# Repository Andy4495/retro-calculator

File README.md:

# Retro Calculator

![Retro Calculator Image][8]

After seeing an Arduino Project Hub [article][5], I purchased a handful of [NSA1166][2] bubble LED displays from [Jameco][3] and decided to build a [retro calculator][8].

The calculator uses an [MSP430G2553][9] microcontroller and [ICM7228][10] LED driver along with a generic 4x4 matrix keypad.

To make the project as small as possible and to simplify the wiring, I created created a PCB design and ordered it from [OshPark][11].

Due to limitations of my keypad and the display (6 characters with a single fixed decimal point), the calculator only supports limited functions and integer math.

## Hardware

The Eagle BRD and SCH files can be found in the [hardware folder][12], along with a PDF of the [schematic][14].

## External Libraries

The calculator uses my [matrix keypad library][1] and [ICM7218 LED driver library][15].

## References

* Arduino Project Hub [article][5]
* NSA-1166 [datasheet][2]
* NSA-1166 devices at [Jameco][3]
* [MSP430G2553][9]
* [ICM7228][10]
* [Schematic][14]
* [Library][4] written specifically for NSA1166, without using discrete controller IC
* Vintage Novus 650 Mathbox [calculator][6] that used the NSA1166 display, including [interior pictures][7]

## License

The software and other files in this repository are released under what is commonly called the [MIT License][100]. See the file [`LICENSE`][101] in this repository.

[1]: https://github.com/Andy4495/matrix-keypad-library
[2]: https://www.jameco.com/Jameco/Products/ProdDS/2210976NAT.pdf
[3]: https://www.jameco.com/z/NSA1166-National-Semiconductor-LED-Display-7-Segment-Red-0-10-Inch-6-Digit-1-65V-5mA-2-Inch-Long_2210976.html
[4]: https://github.com/8bitkick/SevSegPlus
[5]: https://create.arduino.cc/projecthub/8bitkick/retro-led-bubble-display-d357e9
[6]: https://www.keesvandersanden.nl/calculators/novus650.php
[7]: https://www.keesvandersanden.nl/calculators/novus650_inside.php
[8]: ./hardware/Calculator.jpeg
[9]: https://www.ti.com/product/MSP430G2553
[10]: https://www.renesas.com/us/en/www/doc/datasheet/icm7228.pdf
[11]: https://oshpark.com/
[12]: ./hardware
[14]: ./hardware/retro-calculator-schematic.pdf
[15]: https://github.com/Andy4495/ICM7218
[100]: https://choosealicense.com/licenses/mit/
[101]: ./LICENSE
[//]: # ([200]: https://github.com/Andy4495/retro-calculator)

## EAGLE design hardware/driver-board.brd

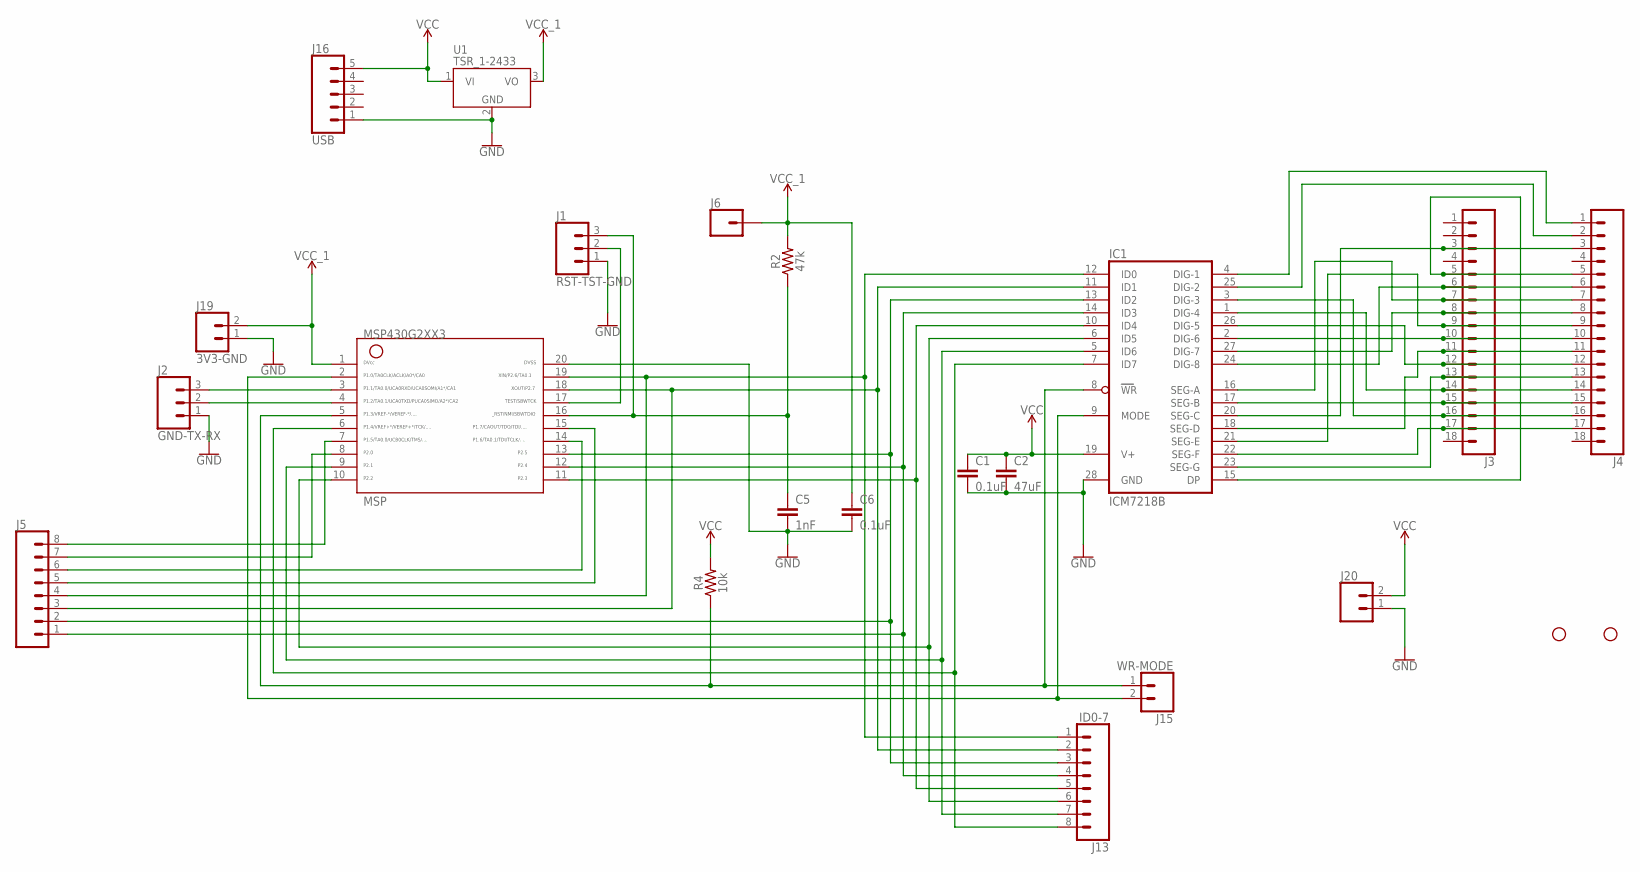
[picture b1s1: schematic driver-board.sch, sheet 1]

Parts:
C1: 0.1uF; C2.5-2
C2: 47uF; C2.5-5
C5: 1nF; C5B2.5
C6: 0.1uF; C5B2.5
H1, H2: STAND-OFF
IC1: ICM7218B; DIL28-6
J1: RST-TST-GND; 1X03_LOCK
J2: GND-TX-RX; 1X03_LOCK
J3, J4: CONN_18; 1X18
J5: CONN_08"; 1X08
J6: CONN_01; 1X01
J13: ID0-7; 1X08_LOCK
J15: WR-MODE; 1X02
J16: USB; 1X05_LOCK
J19: 3V3-GND; 1X02
J20: CONN_02; 1X02
MSP: G2XX3---N20; N20
R2: 47k; AXIAL-0.3
R4: 10k; AXIAL-0.3
U1: TSR_1-2433; TSR-1

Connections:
GND: C1.2, C2.2, C5.2, C6.2, IC1.28 (GND), J1.1, J2.1, J16.1, J19.1, J20.1, MSP.20, U1.2 (GND)
unnamed: IC1.3 (DIG-3), J3.16, J4.16
unnamed: IC1.1 (DIG-4), J3.14, J4.14
unnamed: IC1.26 (DIG-5), J3.12, J4.12
unnamed: J5.8, MSP.7
unnamed: IC1.2 (DIG-6), J3.10, J4.10
unnamed: IC1.27 (DIG-7), J3.8, J4.8
unnamed: IC1.15 (DP), J3.5, J4.5
unnamed: IC1.23 (SEG-G), J3.13, J4.13
unnamed: IC1.24 (DIG-8), J3.6, J4.6
unnamed: IC1.22 (SEG-F), J3.17, J4.17
unnamed: IC1.20 (SEG-C), J3.3, J4.3
unnamed: J5.7, MSP.8
unnamed: IC1.17 (SEG-B), J3.15, J4.15
unnamed: IC1.18 (SEG-D), J3.11, J4.11
unnamed: IC1.21 (SEG-E), J3.9, J4.9
unnamed: IC1.16 (SEG-A), J3.7, J4.7
unnamed: IC1.25 (DIG-2), J4.2
unnamed: IC1.4 (DIG-1), J4.1
unnamed: J2.2, MSP.4
unnamed: J5.6, MSP.14
unnamed: C5.1, J1.3, MSP.16, R2.P$1 (1)
unnamed: J5.5, MSP.15
unnamed: J1.2, MSP.17
unnamed: IC1.14 (ID3), J5.1, J13.4, MSP.12
unnamed: IC1.10 (ID4), J13.5, MSP.11
unnamed: IC1.12 (ID0), J5.4, J13.1, MSP.19
unnamed: IC1.11 (ID1), J5.3, J13.2, MSP.18
unnamed: IC1.6 (ID5), J13.6, MSP.10
unnamed: IC1.5 (ID6), J13.7, MSP.9
unnamed: IC1.7 (ID7), J13.8, MSP.6
unnamed: IC1.8 (WR), J15.1, MSP.5, R4.P$1 (1)
unnamed: IC1.9 (MODE), J15.2, MSP.2
unnamed: J2.3, MSP.3
unnamed: IC1.13 (ID2), J5.2, J13.3, MSP.13
VCC: C1.1, C2.1, IC1.19 (V+), J16.5, J20.2, R4.P$2 (2), U1.1 (VI)
VCC_1: C6.1, J6.1, J19.2, MSP.1, R2.P$2 (2), U1.3 (VO)

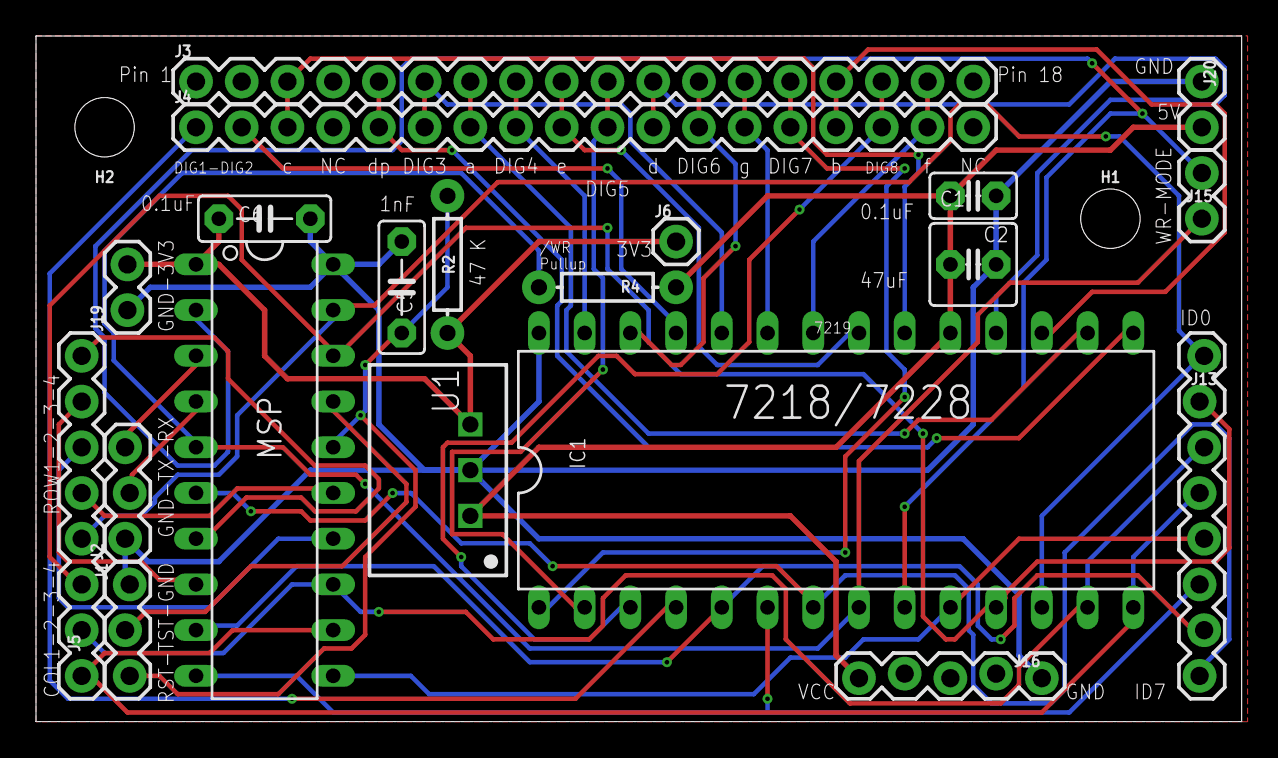
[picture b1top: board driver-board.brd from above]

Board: 2 copper layers, 67.0 x 38.1 mm, 22 parts (0 on the bottom side), 37 nets.

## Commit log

2019-04-12 Original working version.
2019-12-03 Add readme, schematic, eagle files, photo.
2019-12-03 Add image to readme.
2019-12-03 Fix reference links.
2019-12-06 Add reference to ICM7218 library, fix GitHub URL in sketch.
2019-12-07 Use debounce routing from recently updated keypad library.
2021-04-14 Add license info.
2021-04-30 Clean up markdownlint issues.
2022-02-25 Add .gitignore
2022-03-22 Add workflows
2022-03-22 Rename Retro_calculator.ino to retro_calculator.ino
2022-03-22 Rename retro_calculator.ino to retro-calculator.ino
2022-06-06 Change to https
2022-06-18 Add worflow_dispatch from library
2022-06-18 Load board manager URL from GitHub
2022-06-22 Updated package index URL
2022-07-29 Add build matrix avr, msp
2022-08-02 Update for compatibility with nektos/act
2022-09-08 markdownlint issue
2023-02-04 Ignore 403 error in markdown-link-check action
2023-08-25 Update for nektos/act compatibility
2023-08-30 nektos/act compatibility
2023-09-05 Change to reusable workflows
2024-03-08 Update cron time
2024-09-27 Use new Package Index JSON Files
2024-09-30 Switch to lychee for link checks
2025-01-02 Add GCC9 to compile matrix

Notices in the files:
parts and their libraries:
SparkFun-Connectors: Licensing: Creative Commons ShareAlike 4.0 International - https://creativecommons.org/licenses/by-sa/4.0
